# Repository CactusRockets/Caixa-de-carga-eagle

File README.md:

# Caixa de Carregamento

Este repositório contém os arquivos do **esquemático eletrônico** e do **projeto CAD** da caixa de carregamento das aviônicas dos foguetes **Joliot** e **Bouman**.

A caixa de carregamento foi desenvolvida com o objetivo de **facilitar a recarga das baterias das aviônicas**, eliminando a necessidade de removê-las fisicamente do sistema, um processo que pode ser trabalhoso, demorado e pouco prático durante testes e operações.

## Visão Geral do Sistema

O sistema eletrônico da caixa de carregamento é propositalmente simples, robusto e funcional. Ele permite tanto o **monitoramento da tensão das baterias** quanto o **carregamento seguro** das mesmas através de módulos dedicados.

### Componentes Utilizados

* **2× Módulos TP5100** (carregadores de baterias Li-ion/Li-Po): configurados para carregamento 2S (visto que as baterias que serão carregadas estão em série nas aviônicas)
* **2× Módulos voltímetro**
* **1× Fonte de alimentação 12 V**
* **1× Conector de saída** (compatível com o conector presente nas aviônicas)
* **1× Chave tipo alavanca (switch)**

## Esquemático Eletrônico

> **OBS.:** Os arquivos da placa podem ser abertos utilizando o software **Autodesk Eagle**.

## Projeto Mecânico (CAD)

## Funcionamento

Para realizar o carregamento das **quatro baterias presentes na aviônica do Joliot ou do Bouman**, siga os passos abaixo:

1. Conecte a **fonte de 12 V** à tomada e à entrada da caixa de carregamento.
2. Conecte o **conector externo da caixa** à aviônica desejada.
3. Com o **switch desligado**, a caixa opera em **modo de monitoramento**:

   * As próprias baterias da aviônica alimentam os módulos voltímetro.
   * É possível visualizar a **tensão atual das baterias**, permitindo avaliar se o carregamento é necessário.
4. Ao acionar o **switch alavanca**, a caixa entra em **modo de carregamento**:

   * Os módulos **TP5100 passam a carregar as baterias**.
   * O estado do carregamento é indicado pelos LEDs do TP5100:

     * 🔴 **LED vermelho aceso**: bateria em processo de carregamento
     * 🔵 **LED azul aceso**: bateria totalmente carregada

Esse funcionamento torna o processo de recarga **rápido, seguro e intuitivo**, além de reduzir o desgaste mecânico causado pela remoção frequente das baterias da aviônica.

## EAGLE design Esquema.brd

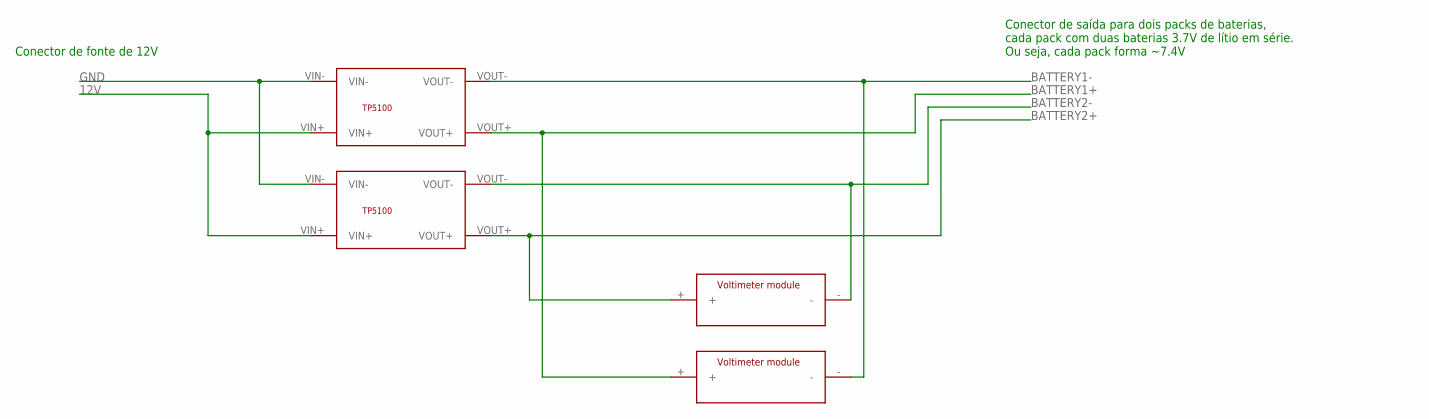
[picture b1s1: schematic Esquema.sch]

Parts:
U$1, U$2: TP5100; TP5100_FOOTPRINT
U$3, U$4: VOLTIMETER_MODULE; VOLTIMETER_MODULE_FOOTPRINT

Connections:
12V: U$1.VIN+, U$2.VIN+
BATTERY1+: U$1.VOUT+, U$4.+
BATTERY1-: U$1.VOUT-, U$4.-
BATTERY2+: U$2.VOUT+, U$3.+
BATTERY2-: U$2.VOUT-, U$3.-
GND: U$1.VIN-, U$2.VIN-

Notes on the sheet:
Conector de fonte de 12V
Conector de saída para dois packs de baterias, cada pack com duas baterias 3.7V de lítio em série. Ou seja, cada pack forma ~7.4V

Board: 2 copper layers, 4 parts (0 on the bottom side), 6 nets, no tracks yet.
